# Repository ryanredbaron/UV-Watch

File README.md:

# UV Watch
## Current MVP
- 10 hours of battery
- Track UV/% burned
- Close enough battery tracking
 
## Project List
1. [x] Clock refinement 
2. [x] Battery shut off
3. [x] Sunscreen apply
4. [ ] Sun reset
5. [x] Less sensitive to sun 
6. [?] Uv sensor voltage revamp
7. [x] Low power mode
8. [x] Input time from PC

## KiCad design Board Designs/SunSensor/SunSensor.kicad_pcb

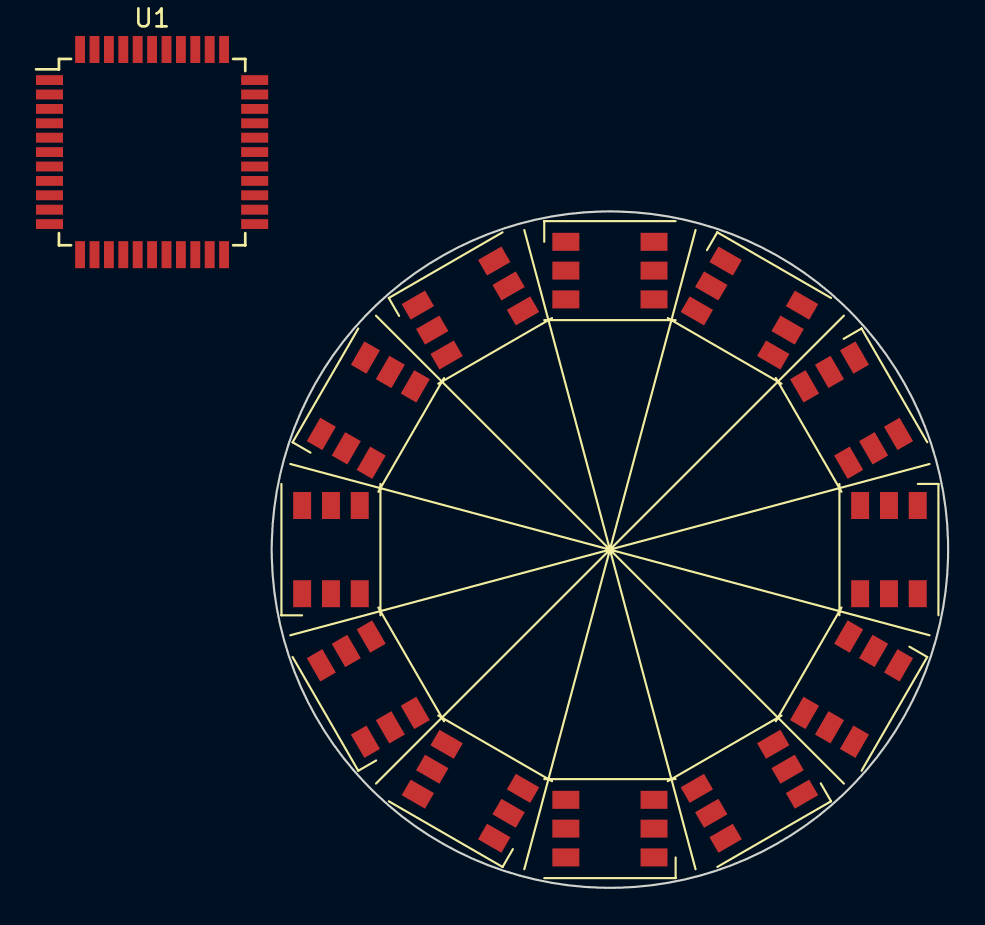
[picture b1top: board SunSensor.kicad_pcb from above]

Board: 2 copper layers, 37.6 x 37.6 mm, 13 parts (0 on the bottom side), 9 nets, no tracks yet.

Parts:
D1, D2, D3, D4, D5, D6, D7, D8, D9, D10, D11, D12: WS2812; LED_WS2812_PLCC6_5.0x5.0mm_P1.6mm
U1: ATmega32U4-AU; TQFP-44_10x10mm_P0.8mm

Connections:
unnamed: D1.1, D2.1, D3.1, D4.1, D5.1, D6.1, D7.1, D8.1, D9.1, D10.1, D11.1, D12.1
unnamed: D1.2, D2.2, D3.2, D4.2, D5.2, D6.2, D7.2, D8.2, D9.2, D10.2, D11.2, D12.2
unnamed: D1.3, D2.3, D3.3, D4.3, D5.3, D6.3, D7.3, D8.3, D9.3, D10.3, D11.3, D12.3
unnamed: D1.4, D2.4, D3.4, D4.4, D5.4, D6.4, D7.4, D8.4, D9.4, D10.4, D11.4, D12.4
unnamed: D1.5, D2.5, D3.5, D4.5, D5.5, D6.5, D7.5, D8.5, D9.5, D10.5, D11.5, D12.5
unnamed: D1.6, D2.6, D3.6, D4.6, D5.6, D6.6, D7.6, D8.6, D9.6, D10.6, D11.6, D12.6
unnamed: U1.14, U1.34
unnamed: U1.15, U1.23, U1.35, U1.43
unnamed: U1.24, U1.44

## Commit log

2019-08-12 Initial Load
2019-08-25 adding eagle files
2019-08-25 V4 hardware
2019-08-25 Moved files
2019-08-26 New board design
2022-09-28 changing to v2
2022-09-28 reading adjustments
2022-10-03 adding sunscreen
2022-10-21 Merging Mark's Firmware
2022-10-21 Updating code
2022-10-21 Combined old features
2022-11-01 Mocap testing
2022-11-10 voltage ref change
2022-11-15 Changing LED update method
2022-11-17 Added Alex's clock
2022-11-19 File structure update
2022-11-21 voltage cutoff, input from PC
2022-11-21 adding long presses
2022-11-21 Sunscreen reporting
2022-11-22 Latching UV
2023-03-06 time adjustments
